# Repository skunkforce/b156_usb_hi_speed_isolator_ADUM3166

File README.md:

# edgy_board number b156
This design is part of the [edgy board project](https://github.com/skunkforce/edgy_boards).

# getting started
This repository uses submodules. After cloning use the command 

```$ git submodule update --init --recursive```

to pull the submodules before opening the project with kicad. 

# Tests
Tests can be found in [TESTS.md](TESTS.md)

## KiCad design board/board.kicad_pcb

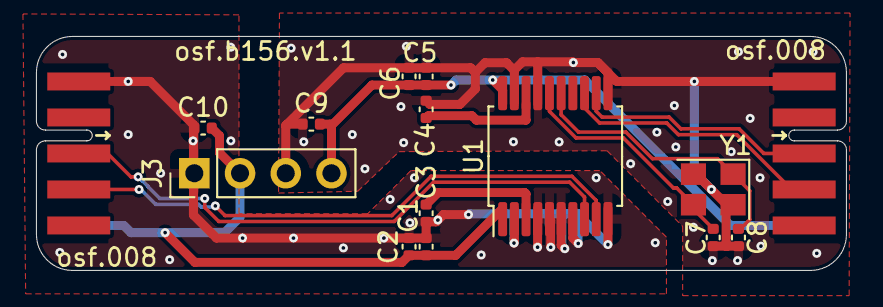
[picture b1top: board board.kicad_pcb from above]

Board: 2 copper layers, 45.0 x 13.0 mm, 16 parts (1 on the bottom side), 12 nets.

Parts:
C1, C3, C4, C6: 100nF; C_0402_1005Metric
C2, C5, C9, C10: 10uF; C_0402_1005Metric
C7, C8: 8pF; C_0402_1005Metric
J1: 008_USB; on_edge_2x05_host
J2: 008_USB; on_edge_2x05_device
J3: B0505M-2WR2; PinHeader_1x04_P2.54mm_Vertical
LOGO1: Logo_Open_Hardware_Small; OSHW-Symbol_6.7x6mm_SilkScreen
U1: ADUM3166; SSOP-20_5.3x7.2mm_P0.65mm
Y1: Crystal_GND24_Small; Crystal_SMD_3225-4Pin_3.2x2.5mm

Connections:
/dcdc/5Vin: C1.1, C2.1, C10.2, J2.10 (5V), J3.2, U1.1 (VBUS1)
/dcdc/5Vout: C5.1, C6.1, C9.2, J1.10 (5V), J3.4, U1.20 (VBUS2)
/dcdc/GND1: C1.2, C2.2, C3.2, C10.1, J2.1 (GND), J3.1, U1.2 (GND1), U1.4 (GND1), U1.5 (GND1), U1.6 (GND1), U1.7 (GND1), U1.10 (GND1)
/dcdc/GND2: C4.2, C5.2, C6.2, C7.2, C8.2, C9.1, J1.1 (GND), J3.3, U1.11 (GND2), U1.17 (GND2), U1.19 (GND2), Y1.2, Y1.4
/iso/D+: J2.3 (DP), U1.8 (UD+)
/iso/D-: J2.4 (DM), U1.9 (UD-)
/iso/DD+: J1.3 (DP), U1.12 (DD+)
/iso/DD-: J1.4 (DM), U1.13 (DD-)
/iso/VDD1: C3.1, U1.3 (VDD1)
/iso/VDD2: C4.1, U1.18 (VDD2)
unnamed: C7.1, U1.16 (XI2), Y1.3
unnamed: C8.1, U1.15 (XO2), Y1.1

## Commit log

2024-02-17 initial
2024-06-23 fixed chip package
